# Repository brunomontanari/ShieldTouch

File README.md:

# ShieldTouch
Full documentation and code to create your own Touch Sense Shield, using any STM32 (64pin package) with the TSC peripheral 

Demonstration Video here: https://drive.google.com/open?id=1O6Jls9418-zFa1CPd3_0eKCgTL7NEVWo

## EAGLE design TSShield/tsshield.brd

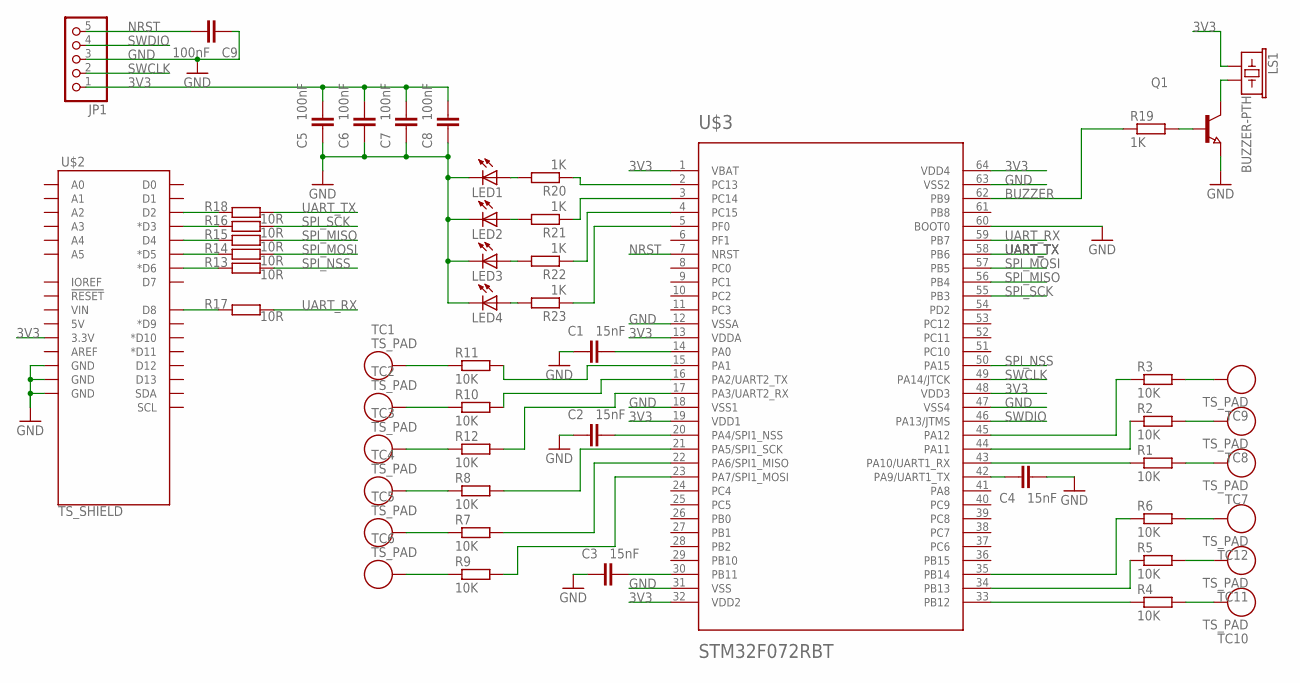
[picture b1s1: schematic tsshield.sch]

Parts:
C1, C2, C3, C4: 15nF; C0603
C5, C6, C7, C8, C9: 100nF; C0603
JP1: PINHD-1X5; 1X05
LED1, LED2, LED3, LED4: LED_E; LED_1206
LS1: BUZZER-PTH; BUZZER-12MM
Q1: NPN-TRANSISTOR_SOT23; SOT23
R1, R2, R3, R4, R5, R6, R7, R8, R9, R10, R11, R12: 10K; R0603
R13, R14, R15, R16, R17, R18: 10R; R0603
R19, R20, R21, R22, R23: 1K; R0603
TC1, TC2, TC3, TC4, TC5, TC6, TC7, TC8, TC9, TC10, TC11, TC12: TS_PAD
U$2: TS_SHIELD
U$3: STM32F072RBT; TQFP64

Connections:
3V3: C5.1, C6.1, C7.1, C8.1, JP1.1, LS1.+ (1), U$2.3.3V, U$3.1 (VBAT), U$3.13 (VDDA), U$3.19 (VDD1), U$3.32 (VDD2), U$3.48 (VDD3), U$3.64 (VDD4)
BUZZER: R19.1, U$3.62 (PB9)
GND: C1.2, C2.2, C3.2, C4.1, C5.2, C6.2, C7.2, C8.2, C9.2, JP1.3, LED1.C, LED2.C, LED3.C, LED4.C, Q1.2 (E), U$2.GND@1 (GND), U$2.GND@2 (GND), U$2.GND@3 (GND), U$3.12 (VSSA), U$3.18 (VSS1), U$3.31 (VSS), U$3.47 (VSS4), U$3.60 (BOOT0), U$3.63 (VSS2)
unnamed: C1.1, U$3.14 (PA0)
unnamed: C2.1, U$3.20 (PA4/SPI1_NSS)
unnamed: C3.1, U$3.30 (PB11)
unnamed: C4.2, U$3.42 (PA9/UART1_TX)
unnamed: R11.2, U$3.15 (PA1)
unnamed: R10.2, U$3.16 (PA2/UART2_TX)
unnamed: R12.2, U$3.17 (PA3/UART2_RX)
unnamed: R8.2, U$3.21 (PA5/SPI1_SCK)
unnamed: R7.1, TC5.1
unnamed: R9.2, U$3.23 (PA7/SPI1_MOSI)
unnamed: R4.1, U$3.33 (PB12)
unnamed: R5.1, U$3.34 (PB13)
unnamed: R6.1, U$3.35 (PB14)
unnamed: R1.1, U$3.43 (PA10/UART1_RX)
unnamed: R2.1, U$3.44 (PA11)
unnamed: R3.1, U$3.45 (PA12)
unnamed: R15.1, U$2.D4
unnamed: R14.1, U$2.D5 (*D5)
unnamed: R13.1, U$2.D6 (*D6)
unnamed: R16.1, U$2.D3 (*D3)
unnamed: R11.1, TC1.1
unnamed: R10.1, TC2.1
unnamed: R12.1, TC3.1
unnamed: R8.1, TC4.1
unnamed: R7.2, U$3.22 (PA6/SPI1_MISO)
unnamed: R9.1, TC6.1
unnamed: R4.2, TC10.1
unnamed: R5.2, TC11.1
unnamed: R6.2, TC12.1
unnamed: R1.2, TC7.1
unnamed: R2.2, TC8.1
unnamed: R3.2, TC9.1
unnamed: R18.1, U$2.D2
unnamed: R17.1, U$2.D8
unnamed: LS1.- (2), Q1.3 (C)
unnamed: Q1.1 (B), R19.2
unnamed: LED2.A, R21.2
unnamed: LED1.A, R20.2
unnamed: LED3.A, R22.2
unnamed: LED4.A, R23.2
unnamed: R20.1, U$3.2 (PC13)
unnamed: R21.1, U$3.3 (PC14)
unnamed: R22.1, U$3.4 (PC15)
unnamed: R23.1, U$3.5 (PF0)
NRST: C9.1, JP1.5, U$3.7 (NRST)
SPI_MISO: R15.2, U$3.56 (PB4)
SPI_MOSI: R14.2, U$3.57 (PB5)
SPI_NSS: R13.2, U$3.50 (PA15)
SPI_SCK: R16.2, U$3.55 (PB3)
SWCLK: JP1.2, U$3.49 (PA14/JTCK)
SWDIO: JP1.4, U$3.46 (PA13/JTMS)
UART_RX: R17.2, U$3.59 (PB7)
UART_TX: R18.2, U$3.58 (PB6)

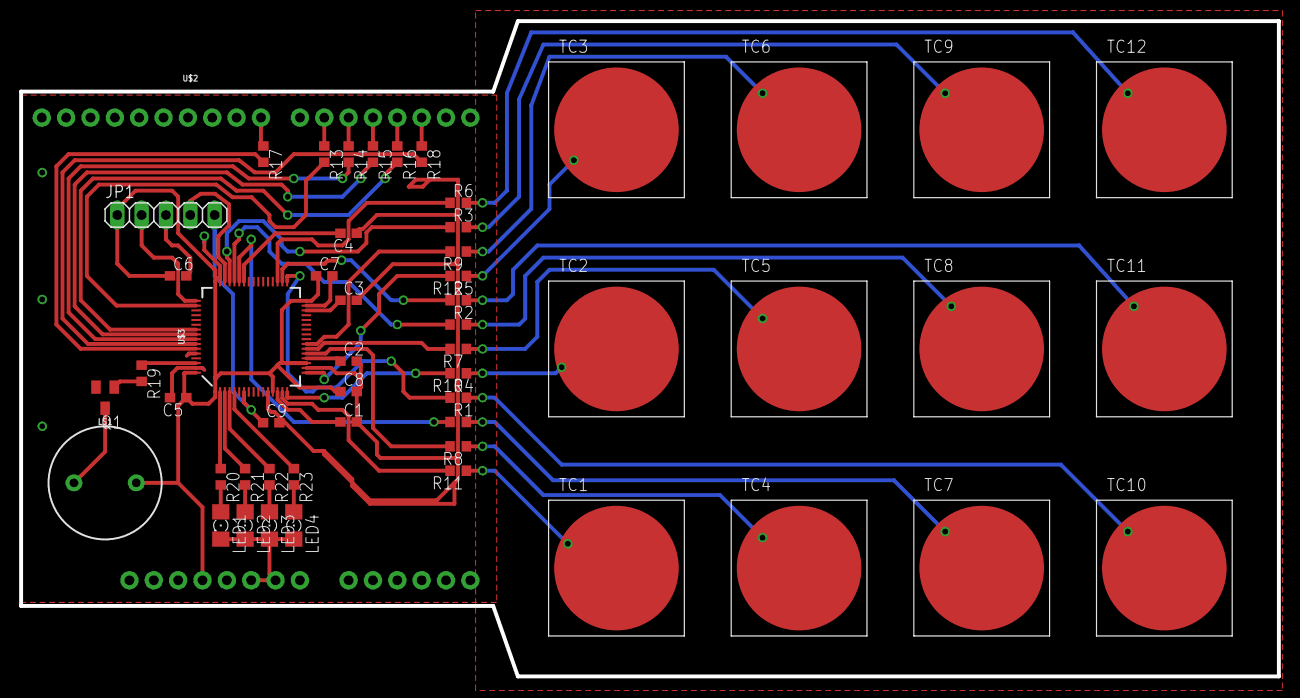
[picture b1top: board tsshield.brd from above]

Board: 2 copper layers, 131.2 x 68.4 mm, 53 parts (0 on the bottom side), 56 nets.

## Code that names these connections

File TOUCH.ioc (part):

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Mcu.Name=STM32F072R(8-B)Tx
Mcu.Package=LQFP64
Mcu.UserName=STM32F072RBTx
PA0.GPIOParameters=GPIO_Speed,GPIO_Label,GPIO_ModeDefaultOD
PA0.GPIO_Label=Ref_1
PA0.GPIO_ModeDefaultOD=GPIO_MODE_AF_OD
PA0.GPIO_Speed=GPIO_SPEED_FREQ_LOW
PA0.Mode=G1_IO1-Sampling
PA0.Signal=TSC_G1_IO1
PA1.GPIOParameters=GPIO_ModeDefaultPP,GPIO_Speed,GPIO_PuPd,GPIO_Label
PA1.GPIO_Label=TC1
PA1.GPIO_ModeDefaultPP=GPIO_MODE_AF_PP
PA1.GPIO_PuPd=GPIO_NOPULL
PA1.GPIO_Speed=GPIO_SPEED_FREQ_LOW
PA1.Mode=G1_IO2-Channel
PA1.Signal=TSC_G1_IO2
PA10.GPIOParameters=GPIO_ModeDefaultPP,GPIO_Speed,GPIO_PuPd,GPIO_Label
PA10.GPIO_Label=TC7
PA10.GPIO_ModeDefaultPP=GPIO_MODE_AF_PP
PA10.GPIO_PuPd=GPIO_NOPULL
PA10.GPIO_Speed=GPIO_SPEED_FREQ_LOW
PA10.Mode=G4_IO2-Channel
PA10.Signal=TSC_G4_IO2
PA11.GPIOParameters=GPIO_ModeDefaultPP,GPIO_Speed,GPIO_PuPd,GPIO_Label
PA11.GPIO_Label=TC8
PA11.GPIO_ModeDefaultPP=GPIO_MODE_AF_PP
PA11.GPIO_PuPd=GPIO_NOPULL
PA11.GPIO_Speed=GPIO_SPEED_FREQ_LOW
PA11.Mode=G4_IO3-Channel
PA11.Signal=TSC_G4_IO3
PA12.GPIOParameters=GPIO_ModeDefaultPP,GPIO_Speed,GPIO_PuPd,GPIO_Label
PA12.GPIO_Label=TC9
PA12.GPIO_ModeDefaultPP=GPIO_MODE_AF_PP
PA12.GPIO_PuPd=GPIO_NOPULL
PA12.GPIO_Speed=GPIO_SPEED_FREQ_LOW
PA12.Mode=G4_IO4-Channel
PA12.Signal=TSC_G4_IO4
PA13.Mode=Serial_Wire
PA13.Signal=SYS_SWDIO
PA14.Mode=Serial_Wire
PA14.Signal=SYS_SWCLK
PA15.GPIOParameters=GPIO_Speed,GPIO_PuPd,GPIO_Mode
PA15.GPIO_Mode=GPIO_MODE_AF_PP
PA15.GPIO_PuPd=GPIO_NOPULL
PA15.GPIO_Speed=GPIO_SPEED_FREQ_LOW
PA15.Mode=NSS_Signal_Hard_Input
PA15.Signal=SPI1_NSS
PA2.GPIOParameters=GPIO_ModeDefaultPP,GPIO_Speed,GPIO_PuPd,GPIO_Label
PA2.GPIO_Label=TC2
PA2.GPIO_ModeDefaultPP=GPIO_MODE_AF_PP
PA2.GPIO_PuPd=GPIO_NOPULL
PA2.GPIO_Speed=GPIO_SPEED_FREQ_LOW
PA2.Mode=G1_IO3-Channel
PA2.Signal=TSC_G1_IO3
PA3.GPIOParameters=GPIO_ModeDefaultPP,GPIO_Speed,GPIO_PuPd,GPIO_Label
PA3.GPIO_Label=TC3
PA3.GPIO_ModeDefaultPP=GPIO_MODE_AF_PP
PA3.GPIO_PuPd=GPIO_NOPULL
PA3.GPIO_Speed=GPIO_SPEED_FREQ_LOW
PA3.Mode=G1_IO4-Channel
PA3.Signal=TSC_G1_IO4
PA4.GPIOParameters=GPIO_Speed,GPIO_Label,GPIO_ModeDefaultOD
PA4.GPIO_Label=Ref_2
PA4.GPIO_ModeDefaultOD=GPIO_MODE_AF_OD
PA4.GPIO_Speed=GPIO_SPEED_FREQ_LOW
PA4.Mode=G2_IO1-Sampling
PA4.Signal=TSC_G2_IO1
PA5.GPIOParameters=GPIO_ModeDefaultPP,GPIO_Speed,GPIO_PuPd,GPIO_Label
PA5.GPIO_Label=TC4
PA5.GPIO_ModeDefaultPP=GPIO_MODE_AF_PP
PA5.GPIO_PuPd=GPIO_NOPULL
PA5.GPIO_Speed=GPIO_SPEED_FREQ_LOW
PA5.Mode=G2_IO2-Channel
PA5.Signal=TSC_G2_IO2
PA6.GPIOParameters=GPIO_ModeDefaultPP,GPIO_Speed,GPIO_PuPd,GPIO_Label
PA6.GPIO_Label=TC5
PA6.GPIO_ModeDefaultPP=GPIO_MODE_AF_PP
PA6.GPIO_PuPd=GPIO_NOPULL
PA6.GPIO_Speed=GPIO_SPEED_FREQ_LOW
PA6.Mode=G2_IO3-Channel
PA6.Signal=TSC_G2_IO3
PA7.GPIOParameters=GPIO_ModeDefaultPP,GPIO_Speed,GPIO_PuPd,GPIO_Label
PA7.GPIO_Label=TC6
PA7.GPIO_ModeDefaultPP=GPIO_MODE_AF_PP
PA7.GPIO_PuPd=GPIO_NOPULL
PA7.GPIO_Speed=GPIO_SPEED_FREQ_LOW
PA7.Mode=G2_IO4-Channel
PA7.Signal=TSC_G2_IO4
PA9.GPIOParameters=GPIO_Speed,GPIO_Label,GPIO_ModeDefaultOD
PA9.GPIO_Label=Ref_3
PA9.GPIO_ModeDefaultOD=GPIO_MODE_AF_OD
PA9.GPIO_Speed=GPIO_SPEED_FREQ_LOW
PA9.Mode=G4_IO1-Sampling
PA9.Signal=TSC_G4_IO1
PB0.Signal=GPIO_Output
PB11.GPIOParameters=GPIO_Speed,GPIO_Label,GPIO_ModeDefaultOD
PB11.GPIO_Label=Ref_4
PB11.GPIO_ModeDefaultOD=GPIO_MODE_AF_OD
PB11.GPIO_Speed=GPIO_SPEED_FREQ_LOW
PB11.Mode=G6_IO1-Sampling
PB11.Signal=TSC_G6_IO1
PB12.GPIOParameters=GPIO_ModeDefaultPP,GPIO_Speed,GPIO_PuPd,GPIO_Label
PB12.GPIO_Label=TC10
PB12.GPIO_ModeDefaultPP=GPIO_MODE_AF_PP
PB12.GPIO_PuPd=GPIO_NOPULL
PB12.GPIO_Speed=GPIO_SPEED_FREQ_LOW
PB12.Mode=G6_IO2-Channel
PB12.Signal=TSC_G6_IO2
PB13.GPIOParameters=GPIO_ModeDefaultPP,GPIO_Speed,GPIO_PuPd,GPIO_Label
PB13.GPIO_Label=TC11
PB13.GPIO_ModeDefaultPP=GPIO_MODE_AF_PP
PB13.GPIO_PuPd=GPIO_NOPULL
PB13.GPIO_Speed=GPIO_SPEED_FREQ_LOW
PB13.Mode=G6_IO3-Channel
PB13.Signal=TSC_G6_IO3
PB14.GPIOParameters=GPIO_ModeDefaultPP,GPIO_Speed,GPIO_PuPd,GPIO_Label
PB14.GPIO_Label=TC12
PB14.GPIO_ModeDefaultPP=GPIO_MODE_AF_PP
PB14.GPIO_PuPd=GPIO_NOPULL
PB14.GPIO_Speed=GPIO_SPEED_FREQ_LOW
PB14.Mode=G6_IO4-Channel
PB14.Signal=TSC_G6_IO4
PB3.GPIOParameters=GPIO_Speed,GPIO_PuPd,GPIO_Mode
PB3.GPIO_Mode=GPIO_MODE_AF_PP
PB3.GPIO_PuPd=GPIO_NOPULL
PB3.GPIO_Speed=GPIO_SPEED_FREQ_LOW
PB3.Mode=Full_Duplex_Master
PB3.Signal=SPI1_SCK
PB4.GPIOParameters=GPIO_Speed,GPIO_PuPd,GPIO_Mode
PB4.GPIO_Mode=GPIO_MODE_AF_PP
PB4.GPIO_PuPd=GPIO_NOPULL
PB4.GPIO_Speed=GPIO_SPEED_FREQ_LOW
PB4.Mode=Full_Duplex_Master
PB4.Signal=SPI1_MISO
PB5.Mode=Full_Duplex_Master
PB5.Signal=SPI1_MOSI
PB6.Mode=Asynchronous
PB6.Signal=USART1_TX
PB7.Mode=Asynchronous
PB7.Signal=USART1_RX
PB9.Signal=S_TIM17_CH1
PC13.Signal=GPIO_Output
PC14-OSC32_IN.Signal=GPIO_Output
PC15-OSC32_OUT.Signal=GPIO_Output
PF0-OSC_IN.Signal=GPIO_Output
RCC.SYSCLKFreq_VALUE=48000000
RCC.SYSCLKSource=RCC_SYSCLKSOURCE_HSI48
board=TOUCH

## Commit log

2017-11-07 Add files via upload
    Schematic, Layout and Gerber files

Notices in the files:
parts and their libraries:
SparkFun-Boards: Licensing: Creative Commons ShareAlike 4.0 International - https://creativecommons.org/licenses/by-sa/4.0
